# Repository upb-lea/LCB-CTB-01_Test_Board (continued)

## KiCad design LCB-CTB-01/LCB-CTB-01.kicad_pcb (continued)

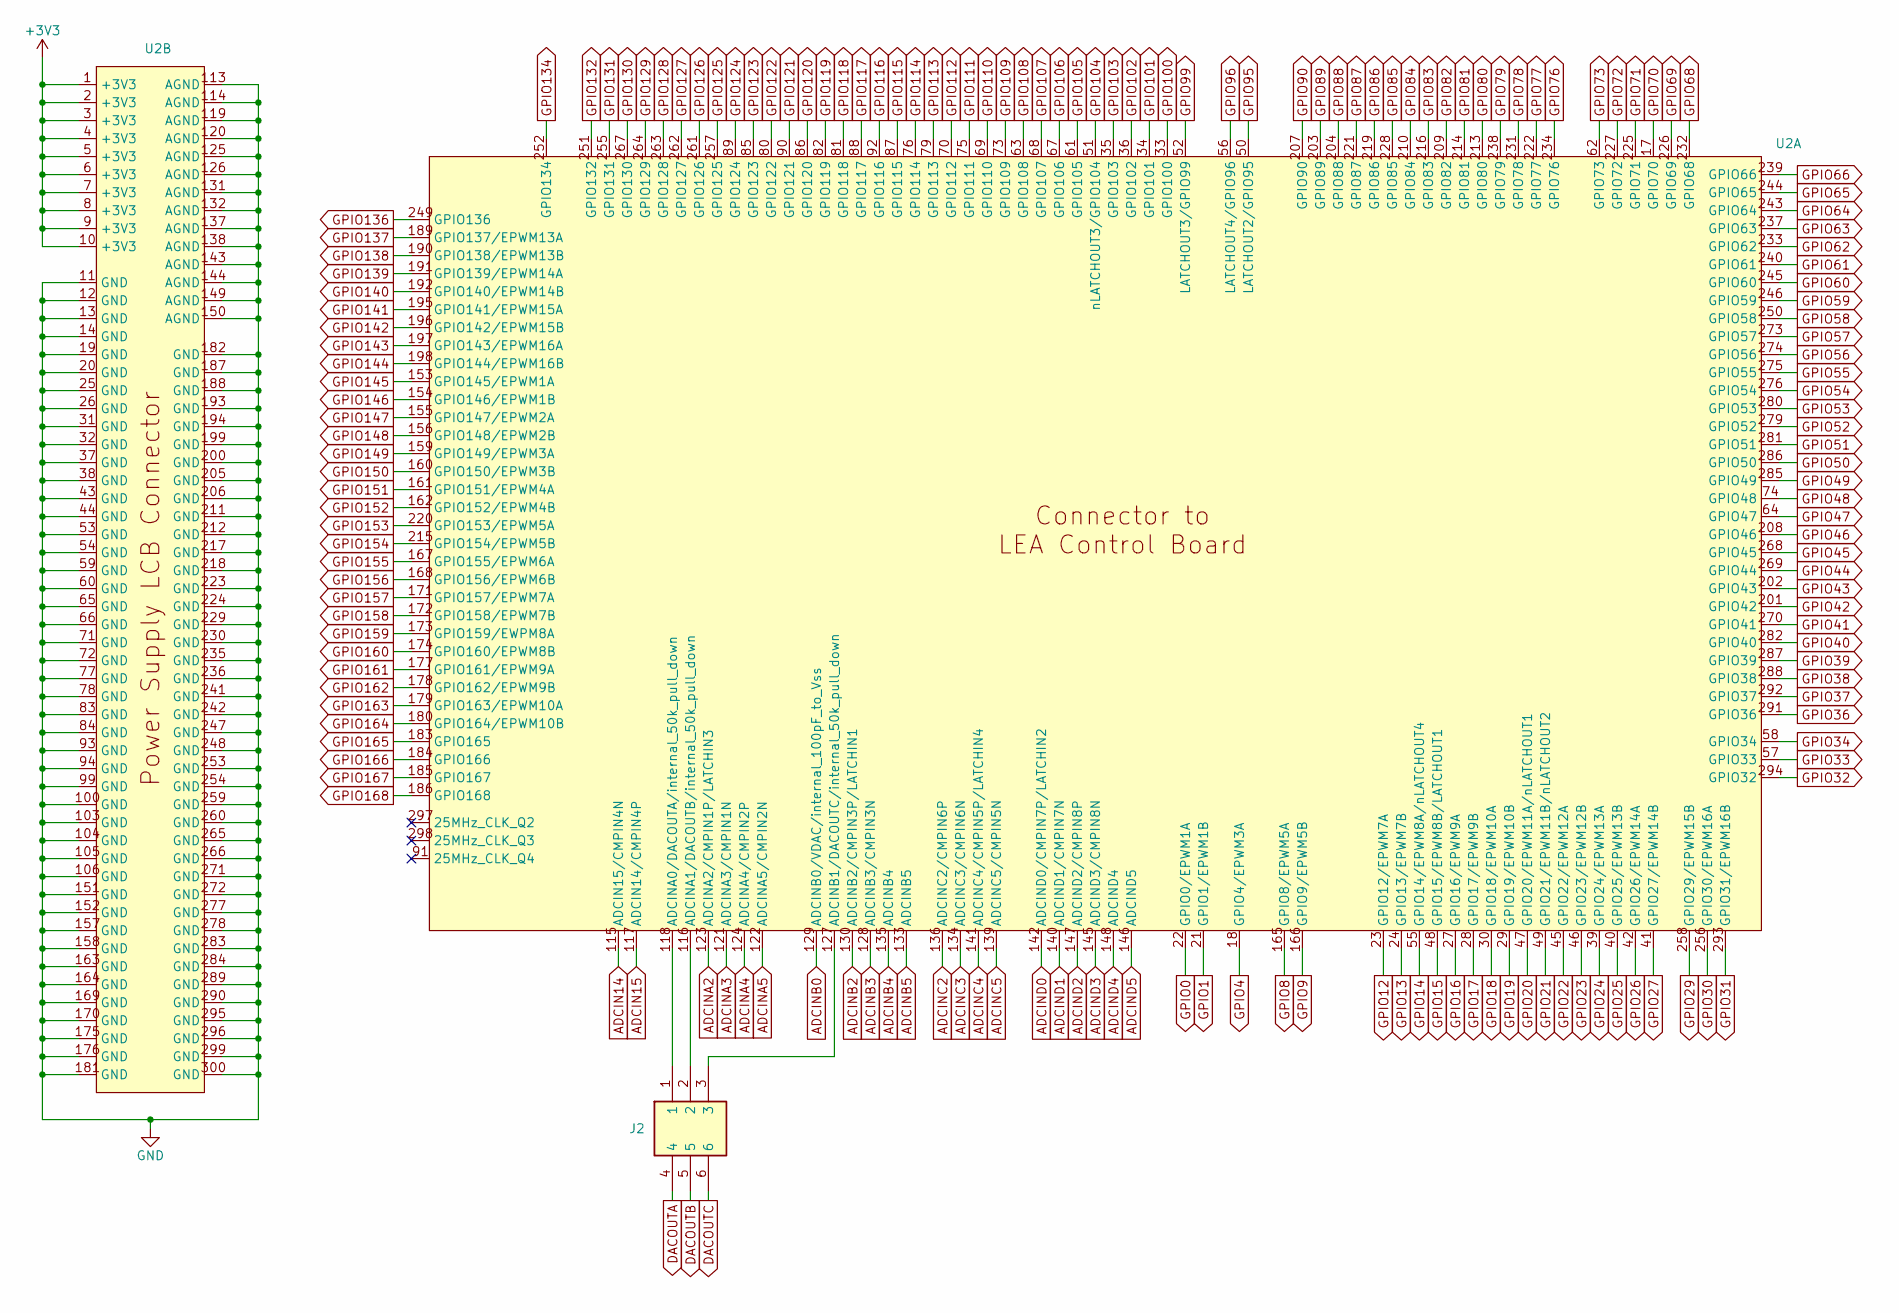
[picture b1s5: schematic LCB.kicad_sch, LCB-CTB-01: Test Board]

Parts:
J2: TSW-102-07-G-T; Conn_02x03; mouser# 200-TSW10207GT
U2: LCB_connector_top; mouser# 200-ERF507505.0LDVTR

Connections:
+3V3: U2.1 (+3V3), U2.2 (+3V3), U2.3 (+3V3), U2.4 (+3V3), U2.5 (+3V3), U2.6 (+3V3), U2.7 (+3V3), U2.8 (+3V3), U2.9 (+3V3), U2.10 (+3V3); also elsewhere on the board
ADCIN14: U2.115 (ADCIN15/CMPIN4N); also elsewhere on the board
ADCIN15: U2.117 (ADCIN14/CMPIN4P); also elsewhere on the board
ADCINA2: U2.123 (ADCINA2/CMPIN1P/LATCHIN3); also elsewhere on the board
ADCINA3: U2.121 (ADCINA3/CMPIN1N); also elsewhere on the board
ADCINA4: U2.124 (ADCINA4/CMPIN2P); also elsewhere on the board
ADCINA5: U2.122 (ADCINA5/CMPIN2N); also elsewhere on the board
ADCINB0: U2.129 (ADCINB0/VDAC/internal_100pF_to_Vss); also elsewhere on the board
ADCINB2: U2.130 (ADCINB2/CMPIN3P/LATCHIN1); also elsewhere on the board
ADCINB3: U2.128 (ADCINB3/CMPIN3N); also elsewhere on the board
ADCINB4: U2.135 (ADCINB4); also elsewhere on the board
ADCINB5: U2.133 (ADCINB5); also elsewhere on the board
ADCINC2: U2.136 (ADCINC2/CMPIN6P); also elsewhere on the board
ADCINC3: U2.134 (ADCINC3/CMPIN6N); also elsewhere on the board
ADCINC4: U2.141 (ADCINC4/CMPIN5P/LATCHIN4); also elsewhere on the board
ADCINC5: U2.139 (ADCINC5/CMPIN5N); also elsewhere on the board
ADCIND0: U2.142 (ADCIND0/CMPIN7P/LATCHIN2); also elsewhere on the board
ADCIND1: U2.140 (ADCIND1/CMPIN7N); also elsewhere on the board
ADCIND2: U2.147 (ADCIND2/CMPIN8P); also elsewhere on the board
ADCIND3: U2.145 (ADCIND3/CMPIN8N); also elsewhere on the board
ADCIND4: U2.148 (ADCIND4); also elsewhere on the board
ADCIND5: U2.146 (ADCIND5); also elsewhere on the board
DACOUTA: J2.4; also elsewhere on the board
DACOUTB: J2.5; also elsewhere on the board
DACOUTC: J2.6; also elsewhere on the board
GND: U2.11 (GND), U2.12 (GND), U2.13 (GND), U2.14 (GND), U2.19 (GND), U2.20 (GND), U2.25 (GND), U2.26 (GND), U2.31 (GND), U2.32 (GND), U2.37 (GND), U2.38 (GND), U2.43 (GND), U2.44 (GND), U2.53 (GND), U2.54 (GND), U2.59 (GND), U2.60 (GND), U2.65 (GND), U2.66 (GND), U2.71 (GND), U2.72 (GND), U2.77 (GND), U2.78 (GND), U2.83 (GND), U2.84 (GND), U2.93 (GND), U2.94 (GND), U2.99 (GND), U2.100 (GND), U2.103 (GND), U2.104 (GND), U2.105 (GND), U2.106 (GND), U2.113 (AGND), U2.114 (AGND), U2.119 (AGND), U2.120 (AGND), U2.125 (AGND), U2.126 (AGND), U2.131 (AGND), U2.132 (AGND), U2.137 (AGND), U2.138 (AGND), U2.143 (AGND), U2.144 (AGND), U2.149 (AGND), U2.150 (AGND), U2.151 (GND), U2.152 (GND), U2.157 (GND), U2.158 (GND), U2.163 (GND), U2.164 (GND), U2.169 (GND), U2.170 (GND), U2.175 (GND), U2.176 (GND), U2.181 (GND), U2.182 (GND), U2.187 (GND), U2.188 (GND), U2.193 (GND), U2.194 (GND), U2.199 (GND), U2.200 (GND), U2.205 (GND), U2.206 (GND), U2.211 (GND), U2.212 (GND), U2.217 (GND), U2.218 (GND), U2.223 (GND), U2.224 (GND), U2.229 (GND), U2.230 (GND), U2.235 (GND), U2.236 (GND), U2.241 (GND), U2.242 (GND), U2.247 (GND), U2.248 (GND), U2.253 (GND), U2.254 (GND), U2.259 (GND), U2.260 (GND), U2.265 (GND), U2.266 (GND), U2.271 (GND), U2.272 (GND), U2.277 (GND), U2.278 (GND), U2.283 (GND), U2.284 (GND), U2.289 (GND), U2.290 (GND), U2.295 (GND), U2.296 (GND), U2.299 (GND), U2.300 (GND); also elsewhere on the board
GPIO0: U2.22 (GPIO0/EPWM1A); also elsewhere on the board
GPIO1: U2.21 (GPIO1/EPWM1B); also elsewhere on the board
GPIO4: U2.18 (GPIO4/EPWM3A); also elsewhere on the board
GPIO8: U2.165 (GPIO8/EPWM5A); also elsewhere on the board
GPIO9: U2.166 (GPIO9/EPWM5B); also elsewhere on the board
GPIO12: U2.23 (GPIO12/EPWM7A); also elsewhere on the board
GPIO13: U2.24 (GPIO13/EPWM7B); also elsewhere on the board
GPIO14: U2.55 (GPIO14/EPWM8A/nLATCHOUT4); also elsewhere on the board
GPIO15: U2.48 (GPIO15/EPWM8B/LATCHOUT1); also elsewhere on the board
GPIO16: U2.27 (GPIO16/EPWM9A); also elsewhere on the board
GPIO17: U2.28 (GPIO17/EPWM9B); also elsewhere on the board
GPIO18: U2.30 (GPIO18/EPWM10A); also elsewhere on the board
GPIO19: U2.29 (GPIO19/EPWM10B); also elsewhere on the board
GPIO20: U2.47 (GPIO20/EPWM11A/nLATCHOUT1); also elsewhere on the board
GPIO21: U2.49 (GPIO21/EPWM11B/nLATCHOUT2); also elsewhere on the board
GPIO22: U2.45 (GPIO22/EPWM12A); also elsewhere on the board
GPIO23: U2.46 (GPIO23/EPWM12B); also elsewhere on the board
GPIO24: U2.39 (GPIO24/EPWM13A); also elsewhere on the board
GPIO25: U2.40 (GPIO25/EPWM13B); also elsewhere on the board
GPIO26: U2.42 (GPIO26/EPWM14A); also elsewhere on the board
GPIO27: U2.41 (GPIO27/EPWM14B); also elsewhere on the board
GPIO29: U2.258 (GPIO29/EPWM15B); also elsewhere on the board
GPIO30: U2.256 (GPIO30/EPWM16A); also elsewhere on the board
GPIO31: U2.293 (GPIO31/EPWM16B); also elsewhere on the board
GPIO32: U2.294 (GPIO32); also elsewhere on the board
GPIO33: U2.57 (GPIO33); also elsewhere on the board
GPIO34: U2.58 (GPIO34); also elsewhere on the board
GPIO36: U2.291 (GPIO36); also elsewhere on the board
GPIO37: U2.292 (GPIO37); also elsewhere on the board
GPIO38: U2.288 (GPIO38); also elsewhere on the board
GPIO39: U2.287 (GPIO39); also elsewhere on the board
GPIO40: U2.282 (GPIO40); also elsewhere on the board
GPIO41: U2.270 (GPIO41); also elsewhere on the board
GPIO42: U2.201 (GPIO42); also elsewhere on the board
GPIO43: U2.202 (GPIO43); also elsewhere on the board
GPIO44: U2.269 (GPIO44); also elsewhere on the board
GPIO45: U2.268 (GPIO45); also elsewhere on the board
GPIO46: U2.208 (GPIO46); also elsewhere on the board
GPIO47: U2.64 (GPIO47); also elsewhere on the board
GPIO48: U2.74 (GPIO48); also elsewhere on the board
GPIO49: U2.285 (GPIO49); also elsewhere on the board
GPIO50: U2.286 (GPIO50); also elsewhere on the board
GPIO51: U2.281 (GPIO51); also elsewhere on the board
GPIO52: U2.279 (GPIO52); also elsewhere on the board
GPIO53: U2.280 (GPIO53); also elsewhere on the board
GPIO54: U2.276 (GPIO54); also elsewhere on the board
GPIO55: U2.275 (GPIO55); also elsewhere on the board
GPIO56: U2.274 (GPIO56); also elsewhere on the board
GPIO57: U2.273 (GPIO57); also elsewhere on the board
GPIO58: U2.250 (GPIO58); also elsewhere on the board
GPIO59: U2.246 (GPIO59); also elsewhere on the board
GPIO60: U2.245 (GPIO60); also elsewhere on the board
GPIO61: U2.240 (GPIO61); also elsewhere on the board
GPIO62: U2.233 (GPIO62); also elsewhere on the board
GPIO63: U2.237 (GPIO63); also elsewhere on the board
GPIO64: U2.243 (GPIO64); also elsewhere on the board
GPIO65: U2.244 (GPIO65); also elsewhere on the board
GPIO66: U2.239 (GPIO66); also elsewhere on the board
GPIO68: U2.232 (GPIO68); also elsewhere on the board
GPIO69: U2.226 (GPIO69); also elsewhere on the board
GPIO70: U2.17 (GPIO70); also elsewhere on the board
GPIO71: U2.225 (GPIO71); also elsewhere on the board
GPIO72: U2.227 (GPIO72); also elsewhere on the board
GPIO73: U2.62 (GPIO73); also elsewhere on the board
GPIO76: U2.234 (GPIO76); also elsewhere on the board
GPIO77: U2.222 (GPIO77); also elsewhere on the board
GPIO78: U2.231 (GPIO78); also elsewhere on the board
GPIO79: U2.238 (GPIO79); also elsewhere on the board
GPIO80: U2.213 (GPIO80); also elsewhere on the board
GPIO81: U2.214 (GPIO81); also elsewhere on the board
GPIO82: U2.209 (GPIO82); also elsewhere on the board
GPIO83: U2.216 (GPIO83); also elsewhere on the board
GPIO84: U2.210 (GPIO84); also elsewhere on the board
GPIO85: U2.228 (GPIO85); also elsewhere on the board
GPIO86: U2.219 (GPIO86); also elsewhere on the board
GPIO87: U2.221 (GPIO87); also elsewhere on the board
GPIO88: U2.204 (GPIO88); also elsewhere on the board
GPIO89: U2.203 (GPIO89); also elsewhere on the board
GPIO90: U2.207 (GPIO90); also elsewhere on the board
GPIO95: U2.50 (LATCHOUT2/GPIO95); also elsewhere on the board
GPIO96: U2.56 (LATCHOUT4/GPIO96); also elsewhere on the board
GPIO99: U2.52 (LATCHOUT3/GPIO99); also elsewhere on the board
GPIO100: U2.33 (GPIO100); also elsewhere on the board
GPIO101: U2.34 (GPIO101); also elsewhere on the board
GPIO102: U2.36 (GPIO102); also elsewhere on the board
GPIO103: U2.35 (GPIO103); also elsewhere on the board
GPIO104: U2.51 (nLATCHOUT3/GPIO104); also elsewhere on the board
GPIO105: U2.61 (GPIO105); also elsewhere on the board
GPIO106: U2.67 (GPIO106); also elsewhere on the board
GPIO107: U2.68 (GPIO107); also elsewhere on the board
GPIO108: U2.63 (GPIO108); also elsewhere on the board
GPIO109: U2.73 (GPIO109); also elsewhere on the board
GPIO110: U2.69 (GPIO110); also elsewhere on the board
GPIO111: U2.75 (GPIO111); also elsewhere on the board
GPIO112: U2.70 (GPIO112); also elsewhere on the board
GPIO113: U2.79 (GPIO113); also elsewhere on the board
GPIO114: U2.76 (GPIO114); also elsewhere on the board
GPIO115: U2.87 (GPIO115); also elsewhere on the board
GPIO116: U2.92 (GPIO116); also elsewhere on the board
GPIO117: U2.88 (GPIO117); also elsewhere on the board
GPIO118: U2.81 (GPIO118); also elsewhere on the board
GPIO119: U2.82 (GPIO119); also elsewhere on the board
GPIO120: U2.86 (GPIO120); also elsewhere on the board
GPIO121: U2.90 (GPIO121); also elsewhere on the board
GPIO122: U2.80 (GPIO122); also elsewhere on the board
GPIO123: U2.85 (GPIO123); also elsewhere on the board
GPIO124: U2.89 (GPIO124); also elsewhere on the board
GPIO125: U2.257 (GPIO125); also elsewhere on the board
GPIO126: U2.261 (GPIO126); also elsewhere on the board
GPIO127: U2.262 (GPIO127); also elsewhere on the board
GPIO128: U2.263 (GPIO128); also elsewhere on the board
GPIO129: U2.264 (GPIO129); also elsewhere on the board
GPIO130: U2.267 (GPIO130); also elsewhere on the board
GPIO131: U2.255 (GPIO131); also elsewhere on the board
GPIO132: U2.251 (GPIO132); also elsewhere on the board
GPIO134: U2.252 (GPIO134); also elsewhere on the board
GPIO136: U2.249 (GPIO136); also elsewhere on the board
GPIO137: U2.189 (GPIO137/EPWM13A); also elsewhere on the board
GPIO138: U2.190 (GPIO138/EPWM13B); also elsewhere on the board
GPIO139: U2.191 (GPIO139/EPWM14A); also elsewhere on the board
GPIO140: U2.192 (GPIO140/EPWM14B); also elsewhere on the board
GPIO141: U2.195 (GPIO141/EPWM15A); also elsewhere on the board
GPIO142: U2.196 (GPIO142/EPWM15B); also elsewhere on the board
GPIO143: U2.197 (GPIO143/EPWM16A); also elsewhere on the board
GPIO144: U2.198 (GPIO144/EPWM16B); also elsewhere on the board
GPIO145: U2.153 (GPIO145/EPWM1A); also elsewhere on the board
GPIO146: U2.154 (GPIO146/EPWM1B); also elsewhere on the board
GPIO147: U2.155 (GPIO147/EPWM2A); also elsewhere on the board
GPIO148: U2.156 (GPIO148/EPWM2B); also elsewhere on the board
GPIO149: U2.159 (GPIO149/EPWM3A); also elsewhere on the board
GPIO150: U2.160 (GPIO150/EPWM3B); also elsewhere on the board
GPIO151: U2.161 (GPIO151/EPWM4A); also elsewhere on the board
GPIO152: U2.162 (GPIO152/EPWM4B); also elsewhere on the board
GPIO153: U2.220 (GPIO153/EPWM5A); also elsewhere on the board
GPIO154: U2.215 (GPIO154/EPWM5B); also elsewhere on the board
GPIO155: U2.167 (GPIO155/EPWM6A); also elsewhere on the board
GPIO156: U2.168 (GPIO156/EPWM6B); also elsewhere on the board
GPIO157: U2.171 (GPIO157/EPWM7A); also elsewhere on the board
GPIO158: U2.172 (GPIO158/EPWM7B); also elsewhere on the board
GPIO159: U2.173 (GPIO159/EWPM8A); also elsewhere on the board
GPIO160: U2.174 (GPIO160/EPWM8B); also elsewhere on the board
GPIO161: U2.177 (GPIO161/EPWM9A); also elsewhere on the board
GPIO162: U2.178 (GPIO162/EPWM9B); also elsewhere on the board
GPIO163: U2.179 (GPIO163/EPWM10A); also elsewhere on the board
GPIO164: U2.180 (GPIO164/EPWM10B); also elsewhere on the board
GPIO165: U2.183 (GPIO165); also elsewhere on the board
GPIO166: U2.184 (GPIO166); also elsewhere on the board
GPIO167: U2.185 (GPIO167); also elsewhere on the board
GPIO168: U2.186 (GPIO168); also elsewhere on the board
unnamed: J2.1, U2.118 (ADCINA0/DACOUTA/internal_50k_pull_down)
unnamed: J2.2, U2.116 (ADCINA1/DACOUTB/internal_50k_pull_down)
unnamed: J2.3, U2.127 (ADCINB1/DACOUTC/internal_50k_pull_down)

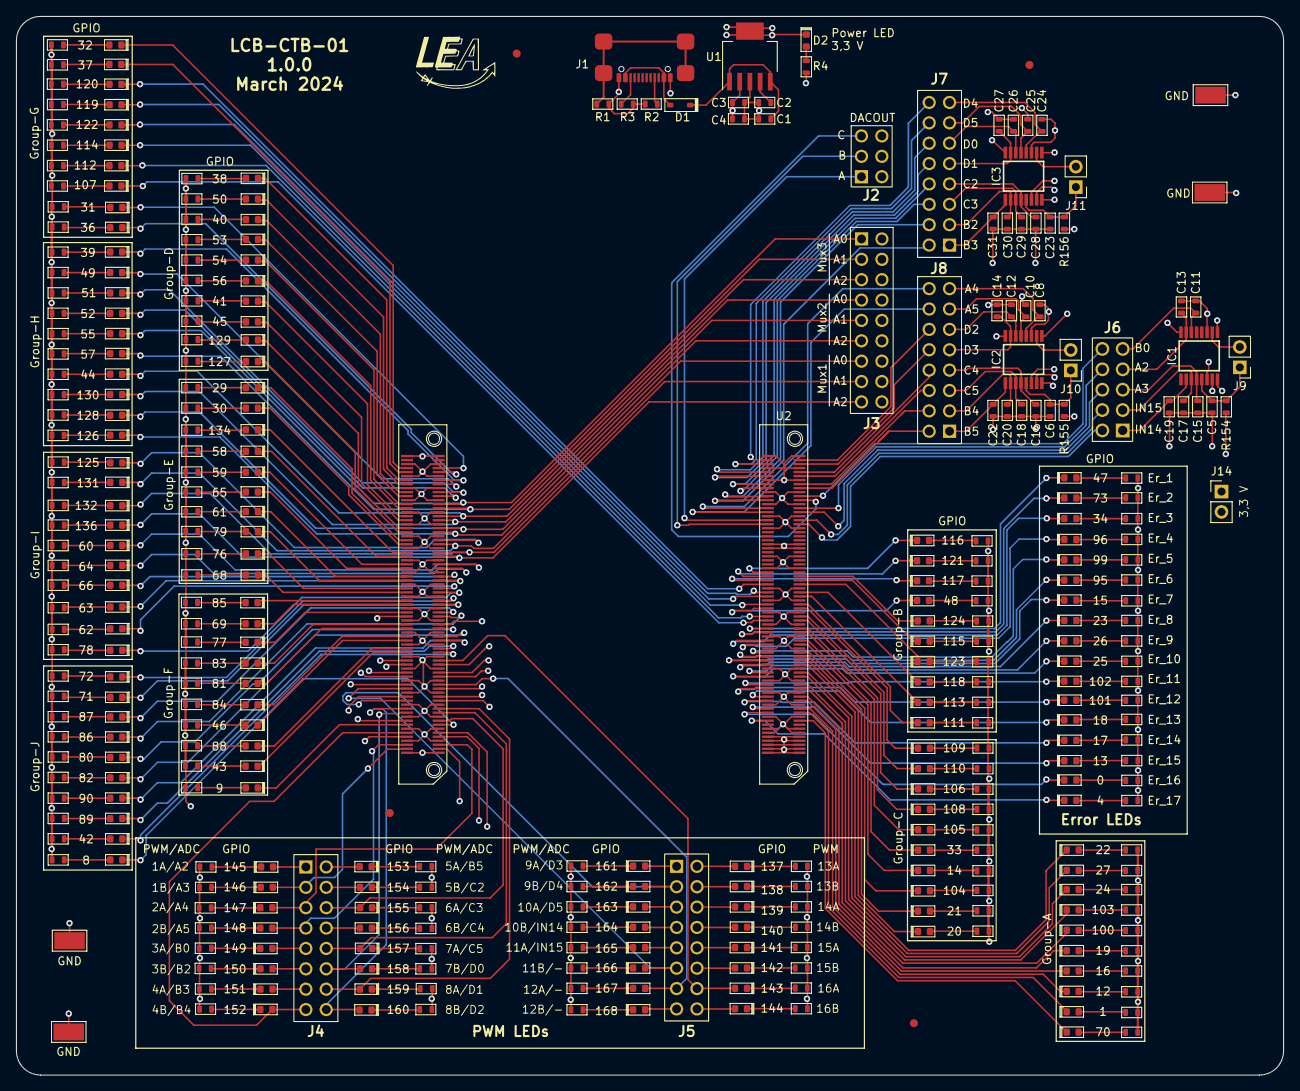
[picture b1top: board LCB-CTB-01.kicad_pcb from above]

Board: 4 copper layers, 158.0 x 132.0 mm, 361 parts (0 on the bottom side), 370 nets.

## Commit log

2024-02-05 add empty project preconfigured
2024-02-08 Add initial schematic files.
2024-02-12 updated_comments-NF-DU
2024-02-25 updated-2502
2024-02-25 updated-25.02
2024-02-26 updated-26.02
2024-02-27 updated on 27.02
2024-02-28 update labeling
2024-02-28 updated on 28.02
2024-03-01 updated on 01.03
2024-03-01 update LED names
2024-03-03 bump version to 1.0.0!
2024-03-03 add documentation
